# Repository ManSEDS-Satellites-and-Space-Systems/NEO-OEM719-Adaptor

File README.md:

# NEO-OEM719-Adaptor

A PCB adaptor for converting NEO series footprint into an OEM719 form factor.

This PCB is also footprint compatible with the SkyTraq S1216, PX1120S and Orion B16.
To use a SkyTraq module, all resistors, capacitors, inductors and eeprom should be removed.

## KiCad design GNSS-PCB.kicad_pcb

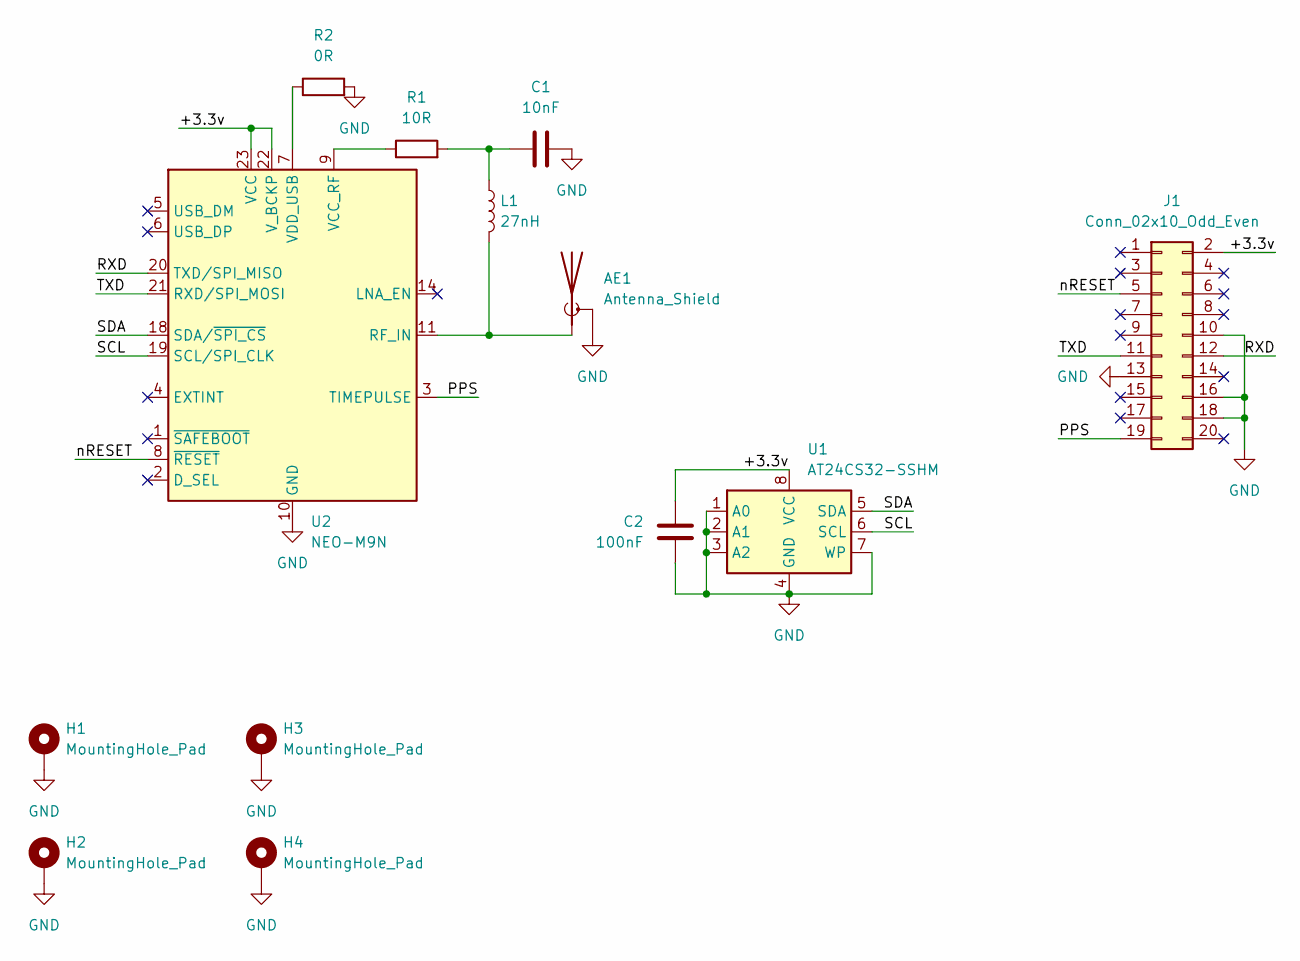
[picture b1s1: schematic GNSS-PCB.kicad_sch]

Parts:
AE1: Antenna_Shield; SAMTEC_MCX-J-P-H-RA-TH1
C1: 10nF; C_0603_1608Metric
C2: 100nF; C_0603_1608Metric
H1, H2, H3, H4: MountingHole_Pad; MountingHole_3.2mm_M3_DIN965_Pad
J1: Conn_02x10_Odd_Even; PinHeader_2x10_P2.00mm_Vertical
L1: 27nH; L_0603_1608Metric
R1: 10R; R_0603_1608Metric
R2: 0R; R_0603_1608Metric
U1: AT24CS32-SSHM; SOIC-8_3.9x4.9mm_P1.27mm
U2: NEO-M9N; ublox_NEO

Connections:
/+3.3v: C2.2, J1.2, U1.8 (VCC), U2.22 (V_BCKP), U2.23 (VCC)
/PPS: J1.19, U2.3 (TIMEPULSE)
/RXD: J1.12, U2.20 (TXD/SPI_MISO)
/SCL: U1.6 (SCL), U2.19 (SCL/SPI_CLK)
/SDA: U1.5 (SDA), U2.18 (SDA/~SPI_CS)
/TXD: J1.11, U2.21 (RXD/SPI_MOSI)
/nRESET: J1.5, U2.8 (~RESET)
GND: AE1.2 (Shield), C1.2, C2.1, H1.1, H2.1, H3.1, H4.1, J1.10, J1.13, J1.16, J1.18, R2.2, U1.1 (A0), U1.2 (A1), U1.3 (A2), U1.4 (GND), U1.7 (WP), U2.10 (GND), U2.12 (GND), U2.13 (GND), U2.24 (GND)
unnamed: AE1.1 (A), L1.2, U2.11 (RF_IN)
unnamed: C1.1, L1.1, R1.2
unnamed: R1.1, U2.9 (VCC_RF)
unnamed: R2.1, U2.7 (VDD_USB)

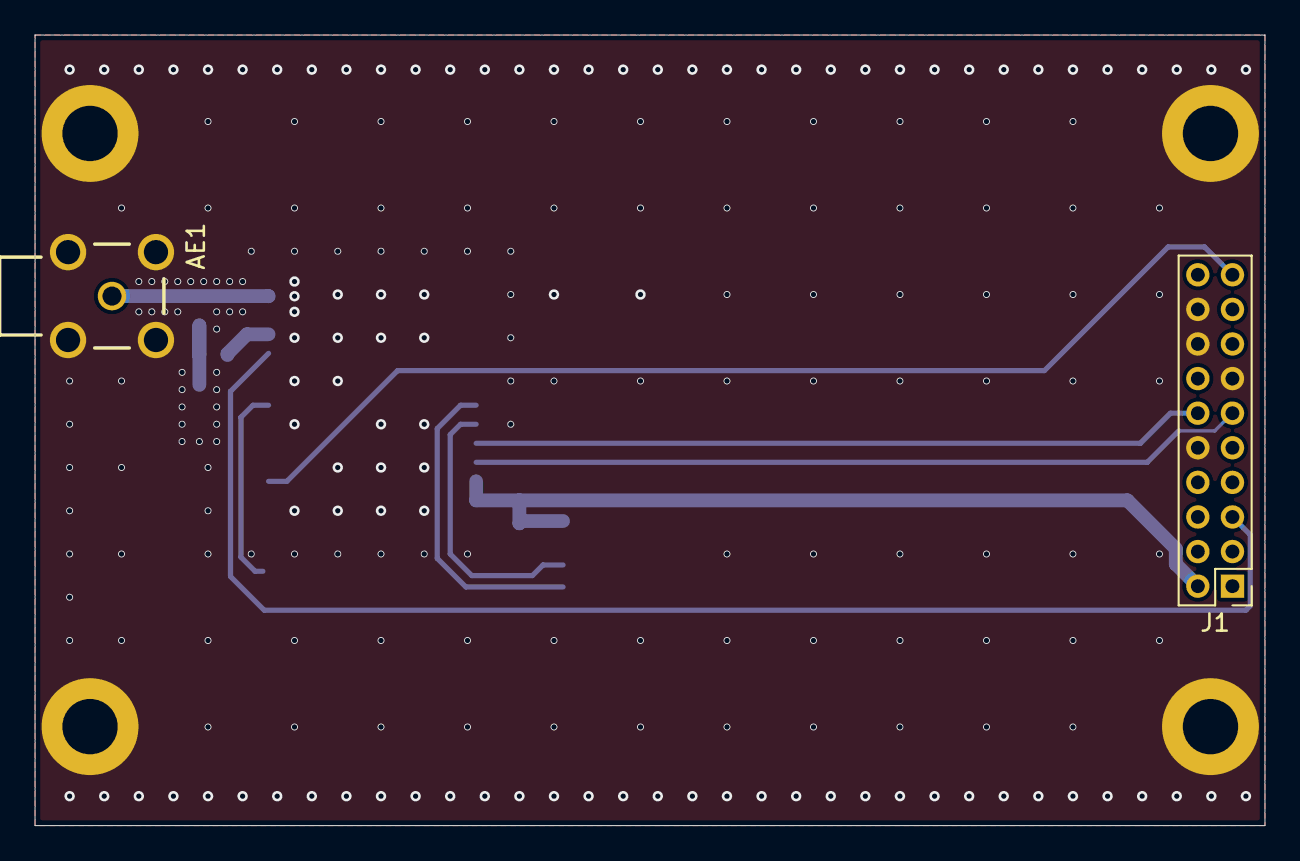
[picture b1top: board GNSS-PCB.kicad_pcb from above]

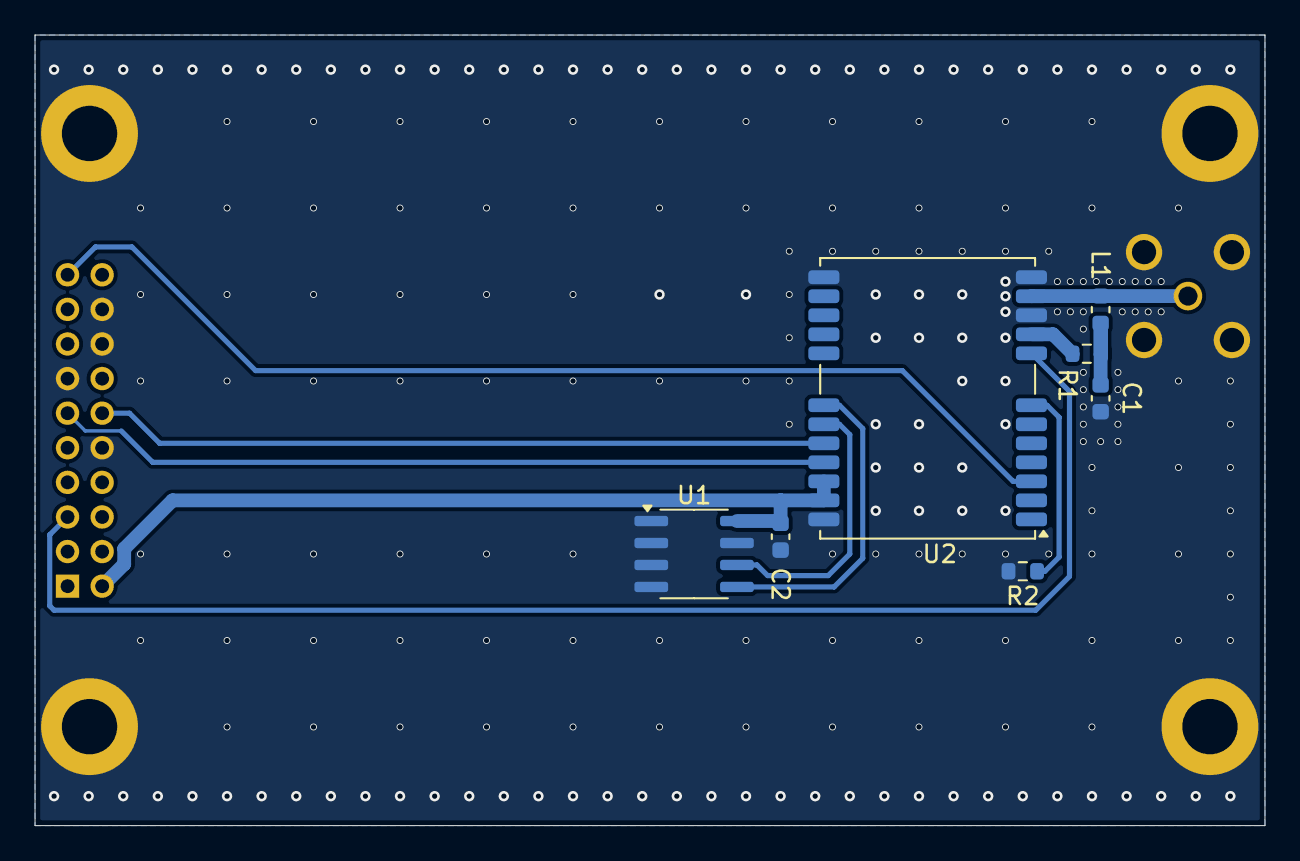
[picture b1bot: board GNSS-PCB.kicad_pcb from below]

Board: 2 copper layers, 71.1 x 45.7 mm, 13 parts (7 on the bottom side), 12 nets.
